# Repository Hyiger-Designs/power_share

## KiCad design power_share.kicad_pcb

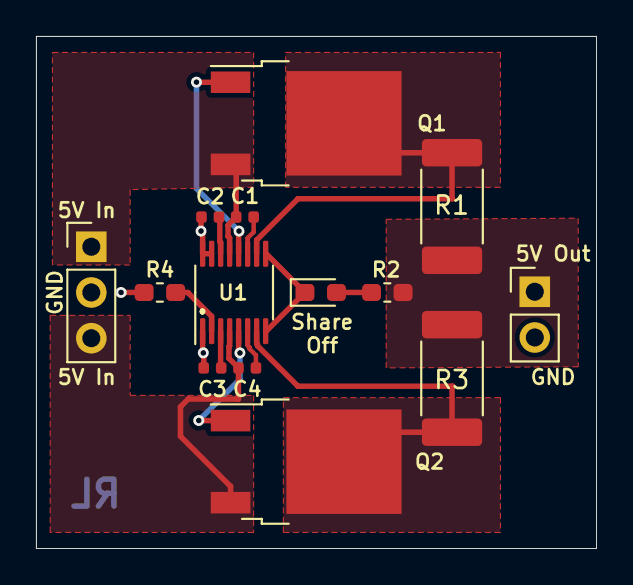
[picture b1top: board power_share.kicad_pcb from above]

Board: 2 copper layers, 31.1 x 28.4 mm, 14 parts (0 on the bottom side), 15 nets.

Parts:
C1, C4: 22nF; C_0402_1005Metric
C2, C3: 100nF; C_0402_1005Metric
D1: LED; LED_0603_1608Metric_Pad1.05x0.95mm_HandSolder
J1: Conn_01x02; PinHeader_1x02_P2.54mm_Vertical
J2: Conn_01x03; PinHeader_1x03_P2.54mm_Vertical
Q1, Q2: IRLR8726PBF; TO-252-2
R1, R3: 2.5m; R_2512_6332Metric_Pad1.52x3.35mm_HandSolder
R2: 820R; R_0603_1608Metric_Pad1.05x0.95mm_HandSolder
R4: 30.1k; R_0603_1608Metric_Pad1.05x0.95mm_HandSolder
U1: LTC4370; MSOP-16_3x4.039mm_P0.5mm

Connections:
5V: J1.1, R1.2, R2.1, R3.1
5V_A: C1.1, J2.1, Q1.3, U1.13
5V_B: C4.2, J2.3, Q2.3, U1.4
GND: C2.2, C3.2, J1.2, J2.2, R4.2, U1.1, U1.15, U1.16
unnamed: C1.2, U1.11
unnamed: C2.1, U1.14
unnamed: C3.1, U1.3
unnamed: C4.1, U1.6
unnamed: D1.1, U1.8, U1.9
unnamed: D1.2, R2.2
unnamed: Q1.1, U1.12
unnamed: Q1.2, R1.1, U1.10
unnamed: Q2.1, U1.5
unnamed: Q2.2, R3.2, U1.7
unnamed: R4.1, U1.2

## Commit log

2019-06-27 initial version
2019-06-27 Added logo
2019-06-27 generated gerbers
2019-06-27 gerber output
2019-06-27 sheet titles
2019-06-28 changed to larger mosfet
2019-06-30 breadboard friendly. fixed dimensions and traces
2019-07-01 final version
2019-07-05 Fixed up wires
2019-07-07 cleaned up layout
2019-07-16 tighten up board
2019-07-21 Redesigned layout
2019-08-13 layout fixes

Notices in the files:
power_share.kicad_pcb:
© Hyiger Designs 2019
